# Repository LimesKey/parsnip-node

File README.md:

# parsnip-node

A rugged, self-contained Meshtastic/MeshCore LoRa node for outdoor use. It combines an
ESP32-S3 host, an Ebyte E22P-915M30S LoRa module (SX1262 + PA, up to 30 dBm / 1 W), and a
u-blox NEO-F10N dual-band (L1 + L5) GNSS receiver, and runs off two 21700 Li-ion cells
in series that charge over USB-C PD or solar. Designed in KiCad for 915 MHz operation in
Canada under ISED RSS-247.

The aim is a node that non-technical people can use without a phone: one of the
longest-range, best-value LoRa front ends, accurate GNSS, days of runtime, and protection
on every external port.

<p align="center">
  <picture>
    <source srcset="lib/img/render-spin.avif" type="image/avif">
    
  </picture>
  <br><sub>Render, see (<a href="code/render/render.sh">code/render</a>), with two 21700 cells and the optional WeAct 3.7" E-Ink module on M2 standoffs and a clear top plate. The display mount is a mock-up, not part of the board yet.</sub>
</p>

## Status

**v2 (this design):** schematic complete, PCB placed and fully routed (478 footprints, every
net one piece of copper). Prototype fab and assembly are being arranged with PCBWay.
Firmware bring-up starts once boards arrive.

**v1** (single 18650, XIAO ESP32-C6, 55 x 100 mm) was built and field-tested; photos are
at the [bottom](#v1-in-the-field). The design log is in [JOURNAL.md](JOURNAL.md).

## Features

| Block | Implementation |
| --- | --- |
| Host | ESP32-S3-WROOM-1U-N16R8 (16 MB flash, 8 MB octal PSRAM), U.FL 2.4 GHz antenna. The footprint is the WROOM-1 land pattern, so the PCB-antenna module also fits. |
| LoRa | E22P-915M30S, 915 MHz, up to 30 dBm, SMA. An antenna-detect FET inhibits TX when no antenna is attached. |
| GNSS | NEO-F10N, L1 + L5 (NEO-M9N footprint-compatible fallback). Active antenna on SMA or U.FL, switched bias-tee, dual-band SAW, 6 dB pi pad. Coin-cell backup for hot starts. |
| Battery | 2S 21700 Li-ion in SMD holders on the back. MAX17320 fuel gauge, protection and cell balancing. |
| Charger | BQ25798 buck-boost NVDC charger with dual-input power mux (USB-C or solar). Regulated ~7-8.4 V system rail. |
| USB-C | TPS25751 PD controller: sink, and source (OTG) up to 20 V @ 3 A. TPD8S300 OVP/ESD on CC/SBU, liquid detection. USB 2.0 full speed to the ESP32-S3. |
| Rails | Two LM61460 low-EMI bucks (5 V, 3.3 V), synchronised 180 deg out of phase at 2 MHz. TPS25947-family eFuses on the 5 V and GNSS rails. |
| Sensors | LSM6DSV16X 6-axis IMU, QMC6309 magnetometer. |
| I/O | 16-pin GPIO expander header (TCAL9539), Qwiic and 2.54 mm I2C ports, SPI expansion, E-Ink header, 2 x WS2816B RGB LEDs plus an external LED port, debug UART. |
| Board | 60 x 130 mm, 4 layers, 1.6 mm, ENIG, black mask. |

All charger and battery-path parts are rated for 4S (caps 25 V minimum, mostly 50 V) even
though the pack is 2S.

## Architecture

<table>
  <tr>
    <td align="center" width="50%">
      
      <br><sub><b>Block diagram</b></sub>
    </td>
    <td align="center" width="50%">
      
      <br><sub><b>Power tree</b></sub>
    </td>
  </tr>
</table>

Power flows cells -> fuse -> MAX17320 protection FETs -> BQ25798 -> **VSYS** (regulated,
not raw battery) -> the 3.3 V and 5 V bucks. The 5 V rail feeds the E22P, the LED port and
the GNSS antenna bias. The GNSS module gets its own LDO and eFuse off 5 V. USB-C (through
the PD controller) and solar each have their own FET path into the charger, and the
first valid input wins.

## Schematic

The full schematic is [parsnip-schematic.pdf](parsnip-schematic.pdf) (12 pages: cover,
block diagram, power tree, then the circuit sheets). Click a page for full size.

<table>
  <tr>
    <td align="center" width="33%">
      
      <br><sub><b>ESP32-S3 MCU</b></sub>
    </td>
    <td align="center" width="33%">
      
      <br><sub><b>LoRa (E22P-915M30S)</b></sub>
    </td>
    <td align="center" width="33%">
      
      <br><sub><b>GNSS (NEO-F10N)</b></sub>
    </td>
  </tr>
  <tr>
    <td align="center" width="33%">
      
      <br><sub><b>5 V / 3.3 V bucks</b></sub>
    </td>
    <td align="center" width="33%">
      
      <br><sub><b>Charger / power path</b></sub>
    </td>
    <td align="center" width="33%">
      
      <br><sub><b>BMS (MAX17320)</b></sub>
    </td>
  </tr>
  <tr>
    <td align="center" width="33%">
      
      <br><sub><b>USB-C / PD</b></sub>
    </td>
    <td align="center" width="33%">
      
      <br><sub><b>Peripherals</b></sub>
    </td>
    <td align="center" width="33%">
      
      <br><sub><b>Connectors</b></sub>
    </td>
  </tr>
</table>

## PCB

<table>
  <tr>
    <td align="center" width="50%">
      <a href="lib/img/render-iso.png"><picture><source srcset="lib/img/render-iso.avif" type="image/avif"></picture></a>
      <br><sub><b>Front</b></sub>
    </td>
    <td align="center" width="50%">
      <a href="lib/img/render-iso-back.png"><picture><source srcset="lib/img/render-iso-back.avif" type="image/avif"></picture></a>
      <br><sub><b>Back</b></sub>
    </td>
  </tr>
  <tr>
    <td align="center" width="50%">
      <a href="lib/img/render-top.png"><picture><source srcset="lib/img/render-top.avif" type="image/avif"></picture></a>
      <br><sub><b>Top</b></sub>
    </td>
    <td align="center" width="50%">
      <a href="lib/img/render-bottom.png"><picture><source srcset="lib/img/render-bottom.avif" type="image/avif"></picture></a>
      <br><sub><b>Bottom (21700 holders)</b></sub>
    </td>
  </tr>
</table>

- 60 x 130 mm, 4 layers, 1.6 mm total, 1 oz copper on all layers, ENIG
- Stackup (JLCPCB `JLC041611-7628` equivalent): F.Cu / 0.203 mm prepreg (Er 4.4) / In1 /
  1.03 mm core / In2 / 0.203 mm prepreg / B.Cu
- In1 is a solid GND reference for all RF. RF lines are 0.306 mm on F.Cu, 49-53 ohm
  field-solved with mask, mostly CPWG with GND via fences well under lambda/20
- ~2100 vias (0.3 mm and 0.2 mm drill), most of them GND stitching
- The cell holders take most of the back, so everything above them is single-sided

## Hardware

| Part | Price |
| --- | --- |
| PCB + assembly ([BOM](production/parsnip-bom.csv)) | being quoted |
| 2 x Samsung 58E 21700 cells [18650batterystore.com](https://www.18650batterystore.com/products/samsung-58e-21700-battery) | $40 CAD |
| WeAct 3.7" E-Ink module, 240 x 416, optional [AliExpress](https://www.aliexpress.com/item/1005009712001279.html?mp=1) | $25 CAD |

Production files (gerbers, BOM, pick-and-place) are in [production/](production/).
Datasheets for every IC, module and connector are in
[docs/datasheets/](docs/datasheets/), sources in
[SOURCES.md](docs/datasheets/SOURCES.md).

## ESP32-S3 GPIO map

GPIO numbers are ESP32-S3 GPIO, not module pins. Reference designators can change during
layout; the schematic is authoritative.

#### LoRa: E22P-915M30S

| Signal | GPIO |
| --- | --- |
| NSS | 10 |
| SCK | 12 |
| MOSI | 11 |
| MISO | 13 |
| BUSY | 14 |
| DIO1 | 4 |
| NRST | 40 |
| EN | 41 |

T/R switching comes from the module's DIO2 (`setDio2AsRfSwitch(true)`), not a GPIO.

#### GNSS: NEO-F10N

| Signal | GPIO |
| --- | --- |
| TXD (to host RX, UART1) | 1 |
| RXD (from host TX, UART1) | 2 |
| TIMEPULSE | 3 |
| EXTINT | 48 |

The module's I2C/SPI pins reach the host I2C bus only through solder jumpers, for the
NEO-M9N fallback. The F10N uses UART only.

#### Other

| Function | GPIO |
| --- | --- |
| I2C SDA / SCL (host bus) | 8 / 9 |
| I2C IRQ (PD controller, fuel gauge, GPIO expander) | 7 |
| E-Ink header: BUSY / RESET / D/C / CS | 5 / 6 / 18 / 17 |
| SPI expansion header CS | 38 |
| USB D- / D+ | 19 / 20 |
| UART0 TX / RX (debug header) | 43 / 44 |
| 32.768 kHz RTC crystal | 15 / 16 |
| BOOT | 0 |
| eFuse power-good: 5 V / GNSS 3.3 V | 39 / 42 |
| EMI sync clock gate | 47 |
| RGB LED data (via 5 V level shifter) | 46 |
| 5 V buck disable (high = off) | 21 |
| Octal PSRAM (reserved) | 35 / 36 / 37 |
| VDD_SPI strap (not connected) | 45 |

#### I2C addresses

| Bus | Device | Address |
| --- | --- | --- |
| Host (GPIO 8/9) | TPS25751 USB-PD controller | 0x20 |
| Host | MAX17320 fuel gauge | 0x36, 0x0B |
| Host | LSM6DSV16X IMU | 0x6A |
| Host | TCAL9539 GPIO expander | 0x74 |
| Host | QMC6309 magnetometer | 0x7C |
| PMIC (owned by the TPS25751) | BQ25798 charger | 0x6B |
| PMIC | M24512 EEPROM (PD config) | 0x50 |

## Firmware

Firmware is a Meshtastic fork, tracked as the `firmware` submodule
([LimesKey/firmware](https://github.com/LimesKey/firmware)). A device variant declares
the pin map above and the PA control lines so TX keys up. The GNSS is on UART1, which
stock Meshtastic supports.

```bash
git clone --recurse-submodules https://github.com/LimesKey/parsnip-node.git
```

## Repository layout

| Path | Contents |
| --- | --- |
| `parsnip.kicad_pro` | KiCad project (KiCad 10.99 nightly format; stable 10.0 cannot open it) |
| `*.kicad_sch` | Schematic sheets: seven top-level sheets plus five sub-sheets under the MCU page |
| `parsnip.kicad_pcb` | Board |
| `lib/` | Project symbols, footprints and 3D models |
| `production/` | Gerbers, BOM, pick-and-place |
| `docs/` | Datasheets and photos |
| `JOURNAL.md` | Design log |
| `v1/` | The previous single-cell board |

## v1 in the field

<table>
  <tr>
    <td align="center" width="33%">
      
      <br><sub><b>Assembled board</b></sub>
    </td>
    <td align="center" width="33%">
      
      <br><sub><b>Outdoor testing</b></sub>
    </td>
    <td align="center" width="33%">
      
      <br><sub><b>Outdoor testing, back</b></sub>
    </td>
  </tr>
</table>

## License

[CC BY-NC-SA 4.0](LICENSE)

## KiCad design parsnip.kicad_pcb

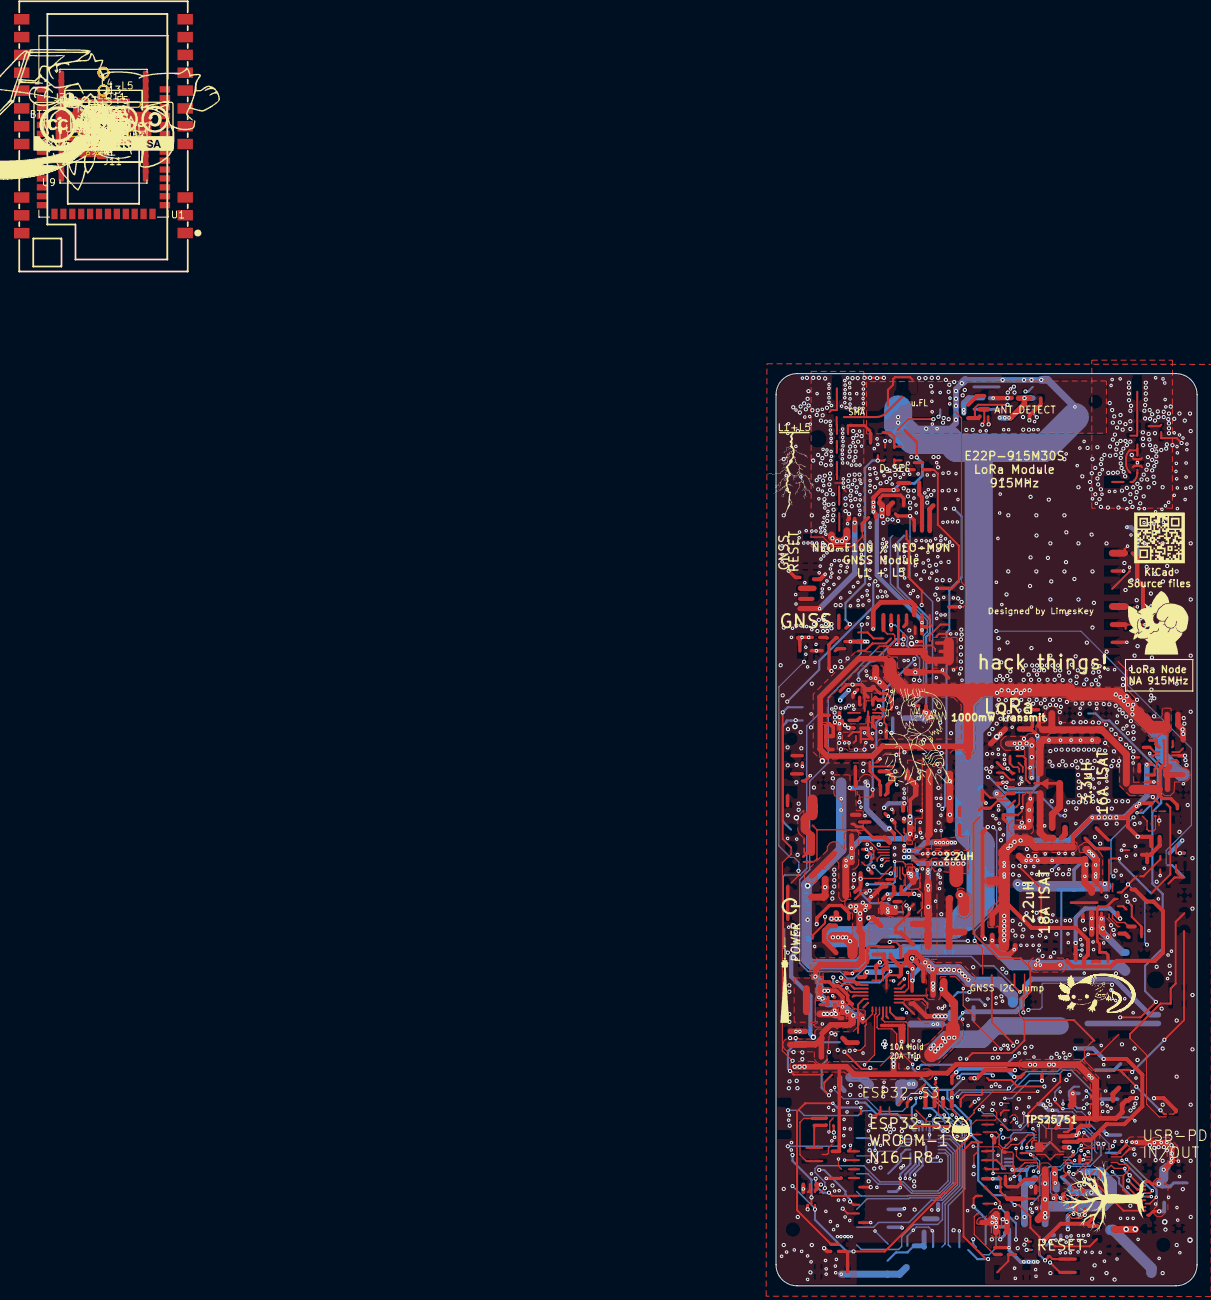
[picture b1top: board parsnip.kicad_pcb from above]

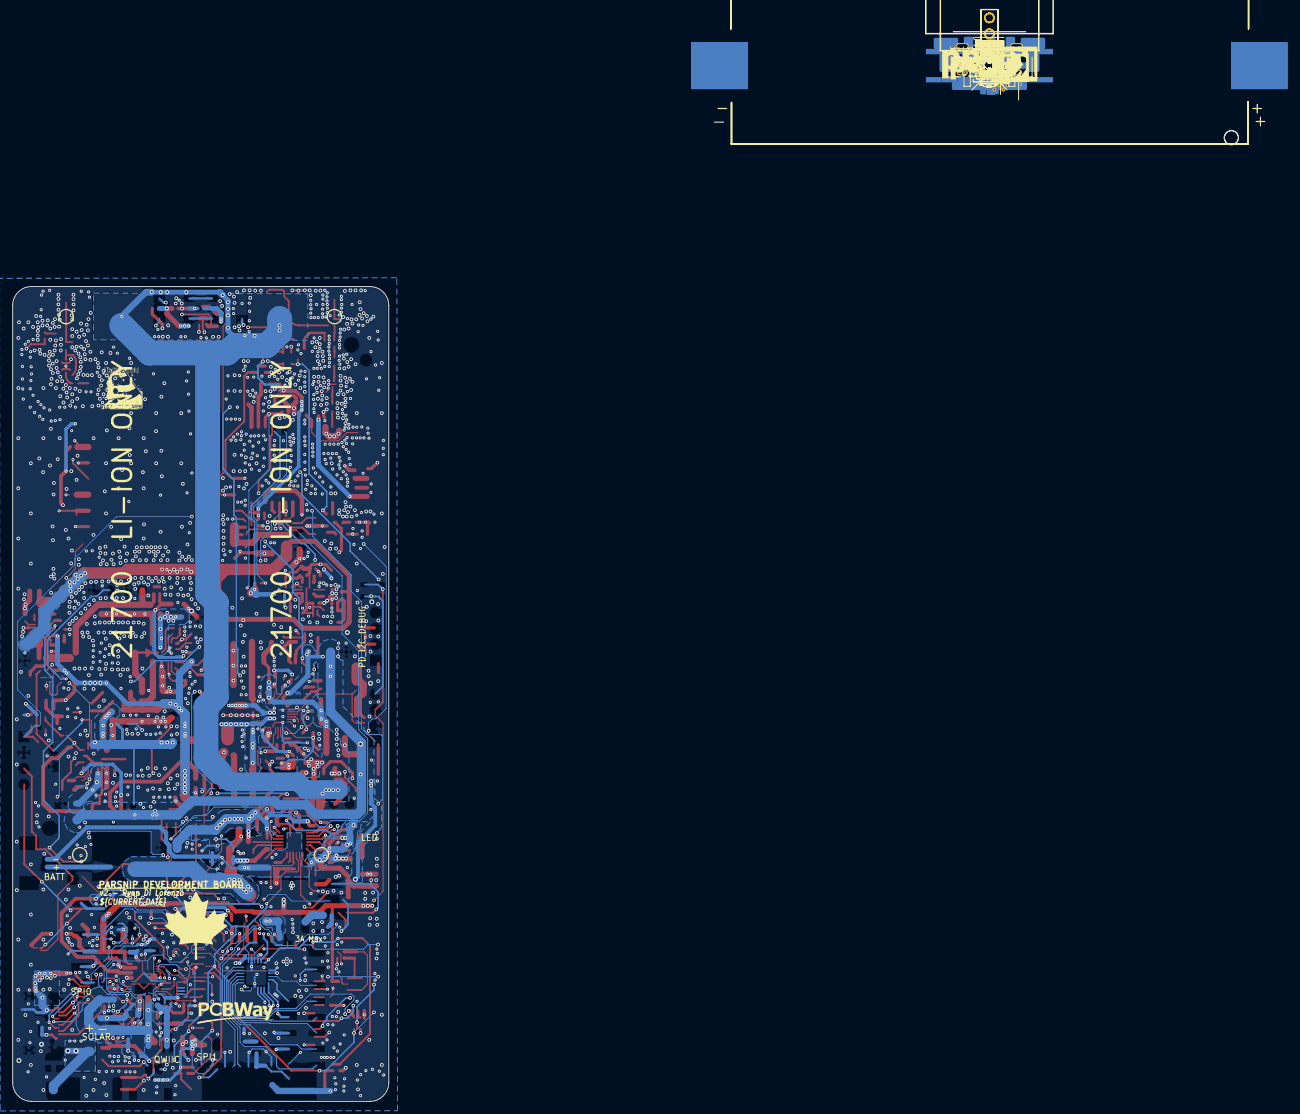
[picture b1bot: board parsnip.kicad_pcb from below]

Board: 4 copper layers, 60.0 x 130.0 mm, 472 parts (71 on the bottom side), 266 nets.

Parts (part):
BOYKISSER: LOGO
BT1, BT2: 21700 Li-ion; BAT-SMD_L82.5.5-W25-BH-21700-B1BJ001
BT3: MS621FE 5.5mAh; BatteryHolder_Seiko_MS621F
C1, C2, C3, C4, C8, C9, C13, C104, C181, C183, C193: 2.2uF; C_0402_1005Metric
C5, C19, C24, C49, C50, C51, C54, C61, C64, C66, C72, C80, C89, C116, C121, C131, C136, C184: 100nF; C_0402_1005Metric
C6, C7: 7pF; C_0402_1005Metric
C10, C11, C12, C16, C110, C122, C123, C124, C126, C127, C128, C137, C141, C143, C156, C168, C169, C177, C187, C188, C189, C190, C191, C192: 10uF; C_0603_1608Metric
C14, C38, C40, C42, C44, C67, C68, C69, C70: 10uF; C_0805_2012Metric
C17, C18, C20, C25, C39, C41, C43, C45, C46, C52, C94, C117, C118, C138, C140, C142, C163, C164, C176, C178, C179, C180, C182: 1uF; C_0402_1005Metric
C21, C22, C23, C47, C98, C105, C132, C134: 10nF; C_0402_1005Metric
C26, C27, C28, C29, C30, C32, C34, C35, C57, C59, C60, C63, C65, C71, C73, C74, C82, C84, C85, C86, C87, C88, C90, C92: 10uF; C_1206_3216Metric
C31: 4.7uF; C_0805_2012Metric
C33, C36: 330pF; C_0402_1005Metric
C37: 1uF; C_0603_1608Metric
C53, C55, C56, C58: 0.47uF; C_0402_1005Metric
C62, C79: 2.2uF; C_0805_2012Metric
C75, C76, C77: 47nF; C_0402_1005Metric
C78: 4.7uF; C_0603_1608Metric
C81: 1nF; C_0402_1005Metric_Pad0.74x0.62mm_HandSolder
C83: 470pF; C_0402_1005Metric_Pad0.74x0.62mm_HandSolder
C93: 22pF; C_0402_1005Metric
C95, C115: 47pF; C_0402_1005Metric
C96, C97: 10nF; C_0402_1005Metric_Pad0.74x0.62mm_HandSolder
C99, C100, C102, C103, C106, C107, C111, C130: 10uF; C_0402_1005Metric
C101: 4.7uF; C_0402_1005Metric
C108, C109, C161, C162: 2.2nF; C_0402_1005Metric
C112, C159, C160: 1nF; C_0402_1005Metric
C113, C114: 1pF; C_0402_1005Metric_Pad0.74x0.62mm_HandSolder
C119, C120: 22uF; C_1206_3216Metric
C125, C129, C135, C145: 2.2uF; C_0603_1608Metric
C133, C139: 220pF; C_0402_1005Metric_Pad0.74x0.62mm_HandSolder
C144, C147, C185: 22uF; C_0805_2012Metric
C153, C158: 5.6pF; C_0402_1005Metric_Pad0.74x0.62mm_HandSolder
C155, C157, C165, C166, C167, C170, C171, C186: 22uF; C_0603_1608Metric
D1, D2, D3, D26, D28, D29: ESDS314DBVR; SOT-23-5
D4, D27: 1N5819WS; D_SOD-323
D6: BZX585-C15; D_SOD-523
D7: TVS2200DRV; WSON-6-1EP_2x2mm_P0.65mm_EP1x1.6mm
D8: CHARGING; LED_0805_2012Metric
D9: SS36B; D_SMB
D10, D13: ESD501; Texas_DPY0002A_0.6x1mm_P0.65mm
D11: POWER; LED_0805_2012Metric
D12: TIMEPULSE; LED_0805_2012Metric
D14: ESD351DPYR; Texas_DPY0002A_0.6x1mm_P0.65mm
D15, D16: RB531SM-30; D_SOD-523
D17, D19: TPD1E10B06; Texas_DPY0002A_0.6x1mm_P0.65mm
D18: PGB1010603; D_0603_1608Metric_Pad1.05x0.95mm_HandSolder
D20: SMF6.0A; D_SOD-123F
D21: BAT54A; SOT-23
D22: BAT54W; SOT-323_SC-70
D23: BAT54S; SOT-23
D24, D25: PZU12B2L; D_SOD-882
F1, F7: 1A hold; Fuse_0805_2012Metric
F2: 2A hold; Fuse_0805_2012Metric
F4: 350mA hold; Fuse_0805_2012Metric
F5: 10A Hold; Fuse_2920_7451Metric
F6: 3A hold; Fuse_1812_4532Metric
FB1: BLM18HG601SN1D; L_0603_1608Metric
FID1, FID2, FID3, FID4, FID5, FID6: Fiducial; Fiducial_1mm_Mask2mm
FL1: B39162B8389P810; Filter_1411-5_1.4x1.1mm_B8389
FL2: 0900LP15B0063001E; FILTER-SMD_0805-8P-L2.0-W1.2-TL
H1, H2, H3, H4: MountingHole_Pad; MountingHole_2.2mm_M2_DIN965_Pad
J1: SPI0; HDR-SMD_6P-P2.54-H-F-W11.7
J2: I2C4; JST_SH_SM04B-SRSS-TB_1x04-1MP_P1.00mm_Horizontal
J3: I2C1; CONN-SMD_4P-P2.54_HX-PM2.54-1X4PWT
J4: I2C2; PinSocket_1x04_P2.54mm_Vertical
J5: SPI1; Molex_PicoBlade_53261-0871_1x08-1MP_P1.25mm_Horizontal
J6: UART0; JST_SH_SM03B-SRSS-TB_1x03-1MP_P1.00mm_Horizontal
J7: USB4105-GF-A-060; USB_C_Receptacle_GCT_USB4105-xx-A_16P_TopMnt_Horizontal
J8: PD_I2C DEBUG; PinSocket_1x04_P2.54mm_Vertical
J9: BAT_PORT; Molex_PicoBlade_53261-0271_1x02-1MP_P1.25mm_Horizontal
J10: SOLAR; JST_PH_S2B-PH-SM4-TB_1x02-1MP_P2.00mm_Horizontal
J11, J13: SMA-KE-347-H13.5-1.6; SMA_Samtec_SMA-J-P-H-ST-EM1_EdgeMount
J12: U.FL; U.FL_Hirose_U.FL-R-SMT-1_Vertical
J14: GPIO_Expander; HDR-SMD_16P-P2.54_HXPM2.54-2X8PWT
J15: LED 5V; JST_XH_S4B-XH-SM4-TB_1x04-1MP_P2.50mm_Horizontal
J16: I2C3; PinSocket_1x04_P2.54mm_Vertical
JP1, JP2: SolderJumper_2_Open; SolderJumper-2_P1.3mm_Open_TrianglePad1.0x1.5mm
JP3: I2C_IRQ_PULLUP; SolderJumper-2_P1.3mm_Bridged_RoundedPad1.0x1.5mm
JP4: I2C_SDA_PULLUP; SolderJumper-2_P1.3mm_Bridged_RoundedPad1.0x1.5mm
JP5: I2C_SCL_PULLUP; SolderJumper-2_P1.3mm_Bridged_RoundedPad1.0x1.5mm
JP6: WRITE_PROTECT; SolderJumper-3_P1.3mm_Bridged12_RoundedPad1.0x1.5mm_NumberL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
JP7: ZVC; SolderJumper-2_P1.3mm_Open_RoundedPad1.0x1.5mm
JP10: SolderJumper_3_Open; SolderJumper-3_P1.3mm_Open_RoundedPad1.0x1.5mm_NumberLabels
JP11: I2C/UART/SPI; SolderJumper-3_P1.3mm_Bridged12_RoundedPad1.0x1.5mm
JP12, JP16: SolderJumper_3_Bridged12; SolderJumper-3_P1.3mm_Bridged12_RoundedPad1.0x1.5mm_NumberL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
JP13: DISABLE_GNSS_PROT; SolderJumper-2_P1.3mm_Open_RoundedPad1.0x1.5mm
JP14: BYPASS_FILTER; R_0402_1005Metric
JP15: ANT_DETECT; SolderJumper-2_P1.3mm_Bridged_RoundedPad1.0x1.5mm
JP17: DISABLE_5V_PROT; SolderJumper-2_P1.3mm_Open_RoundedPad1.0x1.5mm
L1: 2.2uH; L_Sunlord_MWSA0603S
L2: 47nH; L_0603_1608Metric
L3: 470nH; L_0603_1608Metric
L4: 2.2uH; L_APV_APH1040
L5: 3.3uH; L_APV_APH1040
L6, L7: 5.1nH; L_0402_1005Metric
NT1, NT2: NetTie_3; NetTie-3_SMD_Pad0.5mm
Q1, Q3: CSD23280F3; Texas_PicoStar_DFN-3_0.69x0.60mm
Q2, Q4: CSD15380F3; Texas_PicoStar_DFN-3_0.69x0.60mm
Q5, Q6: AON7544; PQFN-8_L3.1-W3.1-P0.65-LS3.3-BL
Q7, Q8: CSD18512Q5B; VSONP-8-1EP_5x6_P1.27mm_CSD18512Q5B
Q9, Q10: SI2308; SOT-23
Q11: CSD17577Q3A; VSON-8_3.3x3.3mm_P0.65mm_NexFET
Q14, Q15: 2N7002; SOT-23
Q16: TPN2R203NC; TSON-8_L3.1-W3.1-P0.65-LS3.3-BL-EP
R1, R2, R3, R4, R23, R60: 33; R_0402_1005Metric_Pad0.72x0.64mm_HandSolder
R5, R6, R12, R13, R14, R15, R18, R19, R32, R33, R34, R69, R73, R93, R134: 0; R_0402_1005Metric
R7, R9, R35, R38, R46, R67, R71, R76, R92, R94, R101, R113, R119, R132, R135: 10k; R_0402_1005Metric
R8: 10M; R_0805_2012Metric
R10, R11: 22; R_0402_1005Metric_Pad0.72x0.64mm_HandSolder
R16, R17, R98: 22; R_0402_1005Metric
R20, R24, R25, R26, R133: 10k; R_0402_1005Metric_Pad0.72x0.64mm_HandSolder
R21, R22, R68, R72: 2.2k; R_0402_1005Metric_Pad0.72x0.64mm_HandSolder
R27, R28, R30, R56, R79, R86, R91, R96, R105, R106, R108, R130, R131, R136: 100k; R_0402_1005Metric
R29, R31, R102: 1M; R_0402_1005Metric
R36, R37: 2.2k; R_0402_1005Metric
R39, R40: 150; R_1206_3216Metric
R41: 5m; R_Shunt_0805_2012Metric_Kelvin
R42, R120: 10; R_0402_1005Metric
R43, R45, R50, R53, R78, R99: 1k; R_0402_1005Metric
R44, R48, R59, R63, R103: 100; R_0402_1005Metric
R47: 330; R_1210_3225Metric
R49, R62: 2; R_0402_1005Metric
R51: 5.23k; R_0603_1608Metric_Pad0.98x0.95mm_HandSolder
R52: 32.4k; R_0603_1608Metric_Pad0.98x0.95mm_HandSolder
R54: 24.3k; R_0603_1608Metric_Pad0.98x0.95mm_HandSolder
R55: 68.1k; R_0603_1608Metric_Pad0.98x0.95mm_HandSolder
R57, R61: 294; R_0402_1005Metric
R58: 8.2k; R_0402_1005Metric_Pad0.72x0.64mm_HandSolder
R64, R65: 2.2; R_0402_1005Metric_Pad0.72x0.64mm_HandSolder
R66: 3k; R_0402_1005Metric_Pad0.72x0.64mm_HandSolder
R70: 2k; R_0402_1005Metric
R74: 10; R_0603_1608Metric_Pad0.98x0.95mm_HandSolder
R75, R95: 0; R_0402_1005Metric_Pad0.72x0.64mm_HandSolder
R80, R83: 150; R_0402_1005Metric_Pad0.72x0.64mm_HandSolder
R81: 37.4; R_0402_1005Metric_Pad0.72x0.64mm_HandSolder
R82: 4.7k; R_0402_1005Metric
R84: 150k; R_0402_1005Metric
R85: 215k; R_0603_1608Metric_Pad0.98x0.95mm_HandSolder
R87: 113k; R_0402_1005Metric_Pad0.72x0.64mm_HandSolder
R88: 6.65k; R_0402_1005Metric_Pad0.72x0.64mm_HandSolder
R89: 200k; R_0603_1608Metric_Pad0.98x0.95mm_HandSolder
R90: 301k; R_0402_1005Metric
R100: 0; R_0805_2012Metric
R104, R107, R115, R121: 402k; R_0603_1608Metric
R109, R110: 6.04k; R_0402_1005Metric_Pad0.72x0.64mm_HandSolder
R111, R117: 100; R_0402_1005Metric_Pad0.72x0.64mm_HandSolder
R112, R118: 2.2; R_0805_2012Metric
R114: 10; R_0402_1005Metric_Pad0.72x0.64mm_HandSolder
R116: 174k; R_0402_1005Metric_Pad0.72x0.64mm_HandSolder
R122: 101k; R_0805_2012Metric_Pad1.20x1.40mm_HandSolder
R123, R124: 1k; R_0402_1005Metric_Pad0.72x0.64mm_HandSolder
R125: 86.6k; R_0402_1005Metric
R126: 3.92k; R_0402_1005Metric
R127: 27.4k; R_0402_1005Metric
R128: 549; R_0402_1005Metric_Pad0.72x0.64mm_HandSolder
R129: 280k; R_0603_1608Metric
RN1: 10k; R_Array_Concave_4x0402
SW1: ESP_RESET; SW_Push_SPST_NO_Alps_SKRK
SW2: BOOT; SW_Push_SPST_NO_Alps_SKRK
SW3: RESET; SW_Push_SPST_NO_Alps_SKRK
SW4: RESET_GNSS; SW_Push_SPST_NO_Alps_SKRK
SW5: SAFEBOOT_GNSS; SW_Push_SPST_NO_Alps_SKRK
TH1, TH2, TH3, TH4, TH5: 10k; R_0603_1608Metric
TP1: R_SENSE_SHUNT; TestPoint_2Pads_Pitch2.54mm_Drill0.8mm
TP2: IN_CP; TestPoint_2Pads_Pitch2.54mm_Drill0.8mm
TP3: REG3; TestPoint_Pad_D1.0mm
TP4: PPHV; TestPoint_2Pads_Pitch2.54mm_Drill0.8mm
TP5: CS_GPS; TestPoint_2Pads_Pitch2.54mm_Drill0.8mm
TP6: SYNC_1; TestPoint_2Pads_Pitch2.54mm_Drill0.8mm
TP7: EN_3V3; TestPoint_Pad_D1.0mm
TP8, TP9: VSYS; TestPoint_2Pads_Pitch2.54mm_Drill0.8mm
TP10, TP11: PGOOD; TestPoint_Pad_D1.5mm
TP12: 3V3; TestPoint_2Pads_Pitch2.54mm_Drill0.8mm
TP13: 5V_RAW; TestPoint_2Pads_Pitch2.54mm_Drill0.8mm
TP14: 5V; TestPoint_2Pads_Pitch2.54mm_Drill0.8mm
TP15: GPIO_EXP_RESET; TestPoint_Pad_D1.5mm
TP16: SYNC_2; TestPoint_2Pads_Pitch2.54mm_Drill0.8mm
U1: ESP32-S3-WROOM-1U-N16R8; ESP32-S3-WROOM-1
U2: QMC6309; QMC6309_WLCSP-4_0.79x0.79mm_P0.4mm
U3: TVS2200DRV; WSON-6-1EP_2x2mm_P0.65mm_EP1x1.6mm
U4: TPD8S300A; WQFN-20_L3.0-W3.0-P0.40-TL-EP1.7
U5: TPS25751DREFR; Texas_REF0038A_WQFN-38-2EP_6x4mm_P0.4
U6, U23: TPS22945DCKR; SOT-353_SC-70-5
U7: MAX17320G22+; QFN-24_L4.0-W4.0-P0.50-BL-EP2.6
U8: BQ25798; Texas_RQM0029A_VQFN-29_4x4mm_P0.4mm
U9: NEO-F10N; ublox_NEO
U10: TPS7A2033PDBVR; SOT-23-5_L2.9-W1.6-P0.95-LS2.8-BR
U11: TPS259474LRPWR; VQFN-10_L2.0-W2.0-P0.45-TL
U12: E22P-915M30S; COMM-SMD_22P-P2.54-L38.5-W24.0_E22-400M33S
U13, U14: LM61460AASQRJRRQ1; VQFN-14-HR_L4.0-W3.5-TL_LM61460AASQRJRRQ1
U15: TPS259474ARPWR; VQFN-10_L2.0-W2.0-P0.45-TL
U16: SN74LVC1G74; X2SON-8_1.4x1mm_P0.35mm
U17: TCAL9539RTWRQ1; TQFN-24_L4.0-W4.0-P0.50-BL-EP2.3
U18, U20: WS2816B; LED-SMD_6P-L5.0-W5.0-TL
U19: 74LV1T34GW; SOT-353_SC-70-5
U21: M24512-DFMC6TG; DFN-8-1EP_3x2mm_P0.5mm_EP1.36x1.46mm
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
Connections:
3V3_GNSS: C99.1, C100.1, C110.2, C111.1, D14.1 (A1), JP10.2 (C), JP13.2 (B), R67.1, R70.1, R76.1, R90.2, R91.1, R136.2, U9.23 (VCC), U11.6 (OUT)
+3V3: C1.1, C2.1, C3.1, C10.1, C11.1, C17.1, C38.1, C39.1, C121.2, C140.1, C144.1, C147.1, C163.1, C164.1, C176.1, C181.2, C183.1, C185.1, C190.2, C191.2, C192.2, C193.1, D4.2 (A), D15.2 (A), D27.2 (A), F1.2, F2.2, F7.2, JP3.2 (B), JP4.2 (B), JP5.2 (B), JP13.1 (A), L4.2, R7.1, R9.1, R24.2, R25.2, R93.1, R96.1, R102.1, R113.1, R114.2, R115.2, R119.1, R123.1, R131.2, R132.1, R133.2, TP12.2, U1.2 (3V3), U2.B1 (VDD), U5.38 (VIN_3V3), U16.6 (~CLR), U16.7 (~PRE), U16.8 (VCC), U17.21 (VCC), U22.5 (VDDIO), U22.8 (VDD), U22.12 (CS), Y2.4 (VDD)
+3V3_EXT: C8.1, C9.1, C142.1, J4.1, J16.1, U23.1 (VOUT)
+5V: C12.1, C16.1, C40.1, C41.1, C165.1, C166.1, C168.1, C169.1, C170.2, C171.2, C178.1, C179.2, C180.1, D20.1 (A1), F6.1, JP12.1 (A), JP17.2 (B), R100.1, R129.2, R134.2, TP14.2, U5.34 (PP5V), U15.6 (OUT), U18.2 (VCC), U19.5 (VCC), U20.2 (VCC)
+BATT: C54.1, C61.1, F5.2, Q5.1 (S), Q5.2 (S), Q5.3 (S)
+PACK: C61.2, C66.1, C67.1, C68.1, C69.1, C70.1, Q6.1 (S), Q6.2 (S), Q6.3 (S), Q11.5 (D), R45.2, R47.2, R63.2
-BATT: C47.2, C50.2, C51.2, C52.2, C55.1, C56.1, C58.1, C98.2, C105.2, C132.2, D6.2 (A), D23.1 (A), Q16.1 (S), Q16.2 (S), Q16.3 (S), R41.1, R43.2, R46.1, TH1.2, TH2.2, TH3.2, TH4.2, TP1.1, U7.20 (GND), U7.25 (EP)
/BMS/BMS_IN: C52.1, C53.1, D23.2 (K), R42.2, TP2.1, U7.1 (IN)
/BMS/CELL_BOT: BT2.2 (-), J9.1, Q16.5 (D), Q16.6 (D), Q16.7 (D), Q16.8 (D), Q16.9 (D)
/BMS/CELL_TOP: BT1.1 (+), F5.1, J9.2, R40.1, R42.1, R135.2
/Charger/ACDRV1: R57.2, U8.11 (ACDRV1)
/Charger/ACDRV2: R61.2, U8.10 (ACDRV2)
/Charger/CHG_BAT: C84.2, C85.2, Q11.1 (S), Q11.2 (S), Q11.3 (S), U8.22 (BAT), U8.23 (BAT)
/Charger/PMID: C80.1, C82.2, C86.2, C87.2, C88.2, U8.29 (PMID)
/Charger/REGN: C78.2, R51.2, R54.1, U8.5 (REGN)
/Charger/SW1: C75.2, L1.1, R65.1, U8.28 (SW1)
/Charger/SW2: C76.1, L1.2, R64.1, U8.26 (SW2)
/Charger/VAC1_MID: D24.2 (A), Q7.1 (S), Q8.1 (S)
/Charger/VAC2_MID: D25.2 (A), Q9.2 (S), Q10.2 (S)
/Root/BOOT: R6.2, R7.2, U1.27 (IO0)
/Root/Connectors/CS_BUS_RAW: D1.5 (I/O4), J1.6, R4.2
/Root/Connectors/I2C_HOST_SCL_RAW: D26.1 (I/O1), D26.5 (I/O4), J2.4, R60.2
/Root/Connectors/I2C_HOST_SDA_RAW: D26.3 (I/O2), D26.4 (I/O3), J2.3, R23.2
/Root/Connectors/MISO_RAW: D1.4 (I/O3), J1.5, R3.2
/Root/Connectors/MOSI_RAW: D1.3 (I/O2), J1.4, R2.2
/Root/Connectors/SCK_RAW: D1.1 (I/O1), J1.3, R1.2
/Root/Connectors/UART0_RX_RAW: D3.3 (I/O2), D3.4 (I/O3), J6.3, R17.2
/Root/Connectors/UART0_TX_RAW: D3.1 (I/O1), D3.5 (I/O4), J6.2, R16.2
/Root/EN: R5.2, R9.2, U1.3 (EN)
/Root/GNSS/D_SEL: JP11.2 (C), U9.2 (D_SEL/(F10:NC))
/Root/GNSS/EXTINT: R53.2, U9.4 (EXTINT)
/Root/GNSS/GNSS_BIAS: C95.2, L2.1, R69.2, R73.2
/Root/GNSS/GNSS_SMA: D10.2 (A2), J11.1 (In), R69.1
/Root/GNSS/GNSS_UFL: D13.1 (A1), J12.1 (In), R73.1
/Root/GNSS/LNA_EN: R78.1, U9.14 (LNA_EN)
/Root/GNSS/RXD/SPI_MOSI: R50.2, U9.21 (RXD/SPI_MOSI)
/Root/GNSS/SCL/SPI_CLK: JP2.2 (B), R72.2, U9.19 (SCL/SPI_CLK/(F10:NC))
/Root/GNSS/SDA/SPI_CS: JP1.2 (B), R68.2, TP5.2, U9.18 (SDA/~SPI_CS/(F10:NC))
/Root/GNSS/VCC_RF: C107.2, D16.2 (A), U9.9 (VCC_RF)
/Root/GPIO_3: R71.1, U1.15 (IO3), U9.3 (TIMEPULSE)
/Root/GPIO_4: U1.4 (IO4), U12.13 (DIO1)
/Root/GPIO_5: J5.1, U1.5 (IO5)
/Root/GPIO_6: J5.2, R26.1, U1.6 (IO6)
/Root/GPIO_10: R96.2, U1.18 (IO10), U12.19 (NSS)
/Root/GPIO_14: U1.22 (IO14), U12.14 (BUSY)
/Root/GPIO_17: J5.4, R24.1, U1.10 (IO17)
/Root/GPIO_18: J5.3, U1.11 (IO18)
/Root/GPIO_21: R103.1, U1.23 (IO21)
/Root/GPIO_38: R4.1, R25.1, U1.31 (IO38)
/Root/GPIO_39: R131.1, U1.32 (IO39), U15.3 (PG/AUXOFF)
/Root/GPIO_40: R19.1, U1.33 (IO40)
/Root/GPIO_41: R18.2, U1.34 (IO41)
/Root/GPIO_42: R91.2, U1.35 (IO42), U11.3 (PG/AUXOFF)
/Root/GPIO_46: U1.16 (IO46), U19.2 (A)
/Root/GPIO_47: D21.1, U1.24 (IO47)
/Root/GPIO_48: R53.1, U1.25 (IO48)
/Root/LoRa/ANT_DETECT: C112.2, Q14.1 (G), R92.1, R102.2
/Root/LoRa/EN: R18.1, R94.2, R101.1, U12.6 (EN)
/Root/LoRa/LORA_5V: C117.1, C118.1, C119.1, C120.1, D19.2 (A2), R100.2, U12.9 (VCC), U12.10 (VCC)
/Root/LoRa/LORA_ANT: C115.1, U12.21 (ANT)
/Root/LoRa/LORA_LPF_IN: C115.2, FL2.8 (IO), JP14.2 (B)
/Root/LoRa/LORA_LPF_OUT: C114.1, FL2.4 (IO), JP14.1 (A), R95.2
/Root/LoRa/LORA_SMA: C113.1, D18.2 (A2), J13.1 (In), L3.2, R95.1
/Root/LoRa/RESET: C116.1, R19.2, U12.15 (NRST)
/Root/P07: R136.1, U6.3 (OC), U17.8 (P07)
/Root/P16: D21.2, R113.2, TP10.1 (1_1), U13.5 (PGOOD), U17.16
/Root/P17: D22.3 (K), R119.2, TP11.1 (1_1), U14.5 (PGOOD), U17.17
/Root/Peripherals/LED_BDO: J15.3, U20.1 (BO), U24.2
/Root/Peripherals/LED_DO: J15.2, U20.3 (DO), U24.1
/Root/Peripherals/P00: J14.1, U17.1 (P00)
/Root/Peripherals/P01: J14.3, U17.2 (P01)
/Root/Peripherals/P02: J14.5, U17.3 (P02)
/Root/Peripherals/P03: J14.7, U17.4 (P03)
/Root/Peripherals/P04: J14.9, U17.5 (P04)
/Root/Peripherals/P05: U17.6 (P05), U22.4 (INT1)
/Root/Peripherals/P06: J14.13, U17.7 (P06)
/Root/Peripherals/P10: J14.2, U17.10
/Root/Peripherals/P11: J14.4, U17.11
/Root/Peripherals/P12: J14.6, U17.12
/Root/Peripherals/P13: J14.8, U17.13
/Root/Peripherals/P14: J14.10, U17.14
/Root/Peripherals/P15: J14.11, U17.15
/Root/Peripherals/RESET_IOEXP: R133.1, TP15.1 (1_1), U17.24 (~RESET)
/Root/Rails/5V_RAW: C155.1, C156.2, C157.1, C167.2, C186.1, C187.2, JP17.1 (A), L5.2, R120.2, R121.2, R124.1, R125.1, TP13.2, U15.5 (IN)
/Root/Rails/SYNC_1: C159.1, Q15.3 (D), R107.2, R108.1, TP6.2, U14.7 (EN/SYNC)
/Root/Rails/SYNC_2: C160.1, JP16.1 (A), TP16.2, U13.7 (EN/SYNC)
/USB Interface/CC1: C36.1, U4.12 (CC1), U5.28 (CC1)
/USB Interface/CC2: C33.1, U4.11 (CC2), U5.29 (CC2)
/USB Interface/C_CC1: J7.A5 (CC1), U4.4 (C_CC1), U4.7 (RPD_G1)
/USB Interface/C_CC2: J7.B5 (CC2), U4.5 (C_CC2), U4.6 (RPD_G2)
/USB Interface/C_SBU1: J7.A8 (SBU1), U4.1 (C_SBU1)
/USB Interface/C_SBU2: J7.B8 (SBU2), U4.2 (C_SBU2)
/USB Interface/FAULT: R27.2, U4.9 (~FLT), U5.19 (GPIO3)
/USB Interface/GPIO2: Q1.1 (G), Q2.1 (G), Q3.1 (G), Q4.1 (G), U5.7 (GPIO2)
/USB Interface/SBU1: R28.2, R29.1, U4.15 (SBU1), U5.26 (GPIO4/USB_P/LD1)
/USB Interface/SBU2: R30.2, R31.1, U4.14 (SBU2), U5.27 (GPIO5/USB_N/LD2)
/USB Interface/WC: JP6.2 (C), U21.7 (WC)
CHG_VBUS: C35.1, C71.2, C72.2, C73.2, C74.2, Q8.3 (D), Q9.3 (D), U8.2 (VBUS), U8.3 (VBUS)
C_USB_B_N: J7.B7 (D-), NT1.3, U4.16 (D4)
C_USB_B_P: J7.B6 (D+), NT2.3, U4.17 (D3)
C_USB_T_N: J7.A7 (D-), NT1.1, U4.19 (D2)
C_USB_T_P: J7.A6 (D+), NT2.1, U4.20 (D1)
GND: BT3.2 (-), C1.2, C2.2, C3.2, C4.2, C5.1, C6.2, C7.1, C8.2, C9.2, C10.2, C11.2, C12.2, C13.2, C14.2, C16.2, C17.2, C18.1, C19.2, C20.2, C21.2, C22.2, C23.2, C24.2, C25.1, C26.2, C27.2, C28.1, C29.2, C30.2, C31.1, C32.2, C33.2, C34.2, C35.2, C36.2, C37.2, C38.2, C39.2, C40.2, C41.2, C42.2, C43.2, C44.2, C45.2, C46.1, C57.1, C59.1, C60.1, C62.2, C63.1, C64.2, C65.1, C66.2, C67.2, C68.2, C69.2, C70.2, C71.1, C72.1, C73.1, C74.1, C77.2, C78.1, C79.2, C80.2, C81.2, C82.1, C83.2, C84.1, C85.1, C86.1, C87.1, C88.1, C89.2, C90.2, C92.2, C93.2, C94.2, C96.2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
GPS_ANT: R81.2, R83.2, U9.11 (RF_IN)
I2C_HOST_IRQ: R20.1, U1.7 (IO7), U5.10 (~I2Ct_IRQ), U7.7 (ALRT), U17.22 (~INT)
I2C_HOST_SCL: D2.1 (I/O1), D28.1 (I/O1), D28.5 (I/O4), D29.1 (I/O1), D29.5 (I/O4), J3.4, J4.3, J16.3, JP2.1 (A), R22.1, R60.1, U1.17 (IO9), U2.A2 (SCL), U5.9 (I2Ct_SCL), U7.8 (SCL/DOD), U17.19 (SCL), U22.13 (SCL)
I2C_HOST_SDA: D2.3 (I/O2), D28.3 (I/O2), D28.4 (I/O3), D29.3 (I/O2), D29.4 (I/O3), J3.2, J4.4, J16.4, JP1.1 (A), R21.1, R23.1, U1.12 (IO8), U2.B2 (SDA), U5.8 (I2Ct_SDA), U7.9 (SDA/DQ), U17.20 (SDA), U22.14 (SDA)
I2C_PMIC_IRQ: R35.2, U5.18 (~I2Cc_IRQ), U8.21 (~INT)
I2C_PMIC_SCL: R32.1, R36.2, U5.17 (I2Cc_SCL), U8.14 (SCL), U21.6 (SCL)
I2C_PMIC_SDA: R33.1, R37.2, U5.16 (I2Cc_SDA), U8.15 (SDA), U21.5 (SDA)
MISO: R3.1, R98.1, U1.21 (IO13)
MOSI: J5.6, R2.1, R10.1, U12.17 (MOSI)
unnamed: BT1.2 (-), BT2.1 (+), R39.1
unnamed: C5.2, R6.1, SW2.2
unnamed: C6.1, R8.2, R12.1, Y1.1
unnamed: C7.2, R8.1, R13.1, Y1.2
unnamed: C62.1, R49.2
unnamed: C79.1, R62.2
unnamed: C81.1, R64.2
unnamed: C83.1, R65.2
unnamed: C93.1, C94.1, L2.2, R74.1
unnamed: C95.1, C96.1, R75.1
unnamed: C97.1, FL1.1, L6.1, R75.2
unnamed: C133.1, R112.2
unnamed: C139.1, R118.2
unnamed: C153.1, R123.2
unnamed: C158.1, R124.2
unnamed: C182.2, R5.1, SW1.2
unnamed: D4.1 (K), F4.2
unnamed: D6.1 (K), Q16.4 (G), R135.1
unnamed: D8.1 (K), R66.1
unnamed: D11.2 (A), R70.2
unnamed: D12.2 (A), R71.2
unnamed: D15.1 (K), R82.1
unnamed: D16.1 (K), JP12.3 (B)
unnamed: C106.2, C130.1, D17.1 (A1), R84.1, R85.1, U10.5 (OUT), U11.5 (IN)
unnamed: D21.3, D22.1 (A), R132.2, Y2.1 (~ST)
unnamed: C49.2, C50.1, D23.3 (COM), R39.2, U7.21 (CELL1)
unnamed: D24.1 (K), Q7.2 (G), Q8.2 (G), R57.1
unnamed: D25.1 (K), Q9.1 (G), Q10.1 (G), R61.1
unnamed: C4.1, D27.1 (K), U23.4 (ON), U23.5 (VIN)
unnamed: FL1.4, L7.1, R80.2, R81.1
unnamed: F1.1, J1.1
unnamed: F7.1, J2.2
unnamed: F2.1, J3.1
unnamed: C13.1, C14.1, F4.1, J5.8
unnamed: J8.1, R34.1
unnamed: J8.2, R32.2
unnamed: J8.3, R33.2
unnamed: C137.1, F6.2, J15.1
unnamed: JP3.1 (A), R20.2
unnamed: JP4.1 (A), R21.2
unnamed: JP5.1 (A), R22.2
unnamed: JP6.1 (A), RN1.8 (R1.2)
unnamed: JP6.3 (B), R38.1
unnamed: JP7.1 (A), U7.5 (ZVC)
unnamed: JP7.2 (B), R47.1
unnamed: JP10.1 (A), R72.1
unnamed: JP10.3 (B), R68.1
unnamed: JP11.1 (A), R67.2
unnamed: FB1.2, JP12.2 (C)
unnamed: JP15.2 (B), Q14.2 (S)
unnamed: JP16.3 (B), TP7.1 (1_1)
unnamed: JP16.2 (C), R104.2, R105.1
unnamed: L3.1, R92.2
unnamed: Q1.3 (D), R28.1
unnamed: Q2.3 (D), R29.2
unnamed: Q3.3 (D), R30.1
unnamed: Q4.3 (D), R31.2
unnamed: Q5.5 (D), Q5.6 (D), Q5.7 (D), Q5.8 (D), Q6.5 (D), Q6.6 (D), Q6.7 (D), Q6.8 (D)
unnamed: C54.2, Q5.4 (G), R44.2
unnamed: Q6.4 (G), R48.2
unnamed: Q11.4 (G), U8.24 (SDRV)
unnamed: Q14.3 (D), R99.2, U12.7 (T/RCTRL)
unnamed: Q15.1 (G), R103.2, R106.1
unnamed: R59.1, SW3.2
unnamed: R93.2, R94.1
unnamed: RN1.7 (R2.2), U21.1 (E0)
unnamed: RN1.6 (R3.2), U21.2 (E1)
unnamed: RN1.5 (R4.2), U21.3 (E2)
unnamed: R10.2, U1.19 (IO11)
unnamed: R11.2, U1.20 (IO12)
unnamed: R12.2, U1.8 (IO15)
unnamed: R13.2, U1.9 (IO16)
unnamed: R15.1, U1.14 (USB_D+)
unnamed: R14.1, U1.13 (USB_D-)
unnamed: C19.1, U4.3 (VBIAS)
unnamed: U5.15 (DRAIN), U5.30 (DRAIN), U5.40 (DRAIN)
unnamed: C42.1, C43.1, U5.4 (LDO_1V5)
unnamed: R78.2, R79.2, U6.4 (ON)
unnamed: C101.1, FB1.1, U6.5 (VIN)
unnamed: C138.1, R74.2, U6.1 (VOUT)
unnamed: C58.2, R46.2, U7.12 (AOLDO)
unnamed: C49.1, C51.1, R40.2, U7.22 (CELL2), U7.23 (CELL3), U7.24 (BATTS)
unnamed: R44.1, U7.3 (CHG)
unnamed: C53.2, TP2.2, U7.2 (CP)
unnamed: R41.3, U7.14 (CSN)
unnamed: R41.2, U7.15 (CSP)
unnamed: R48.1, U7.4 (DIS)
unnamed: R45.1, U7.6 (PCKP)
unnamed: R43.1, U7.11 (PFAIL)
unnamed: C55.2, U7.17 (REG2)
unnamed: C56.2, TP3.1 (1_1), U7.13 (REG3)
unnamed: C98.1, TH1.1, U7.10 (TH1)
unnamed: C132.1, TH2.1, U7.16 (TH2)
unnamed: C105.1, TH3.1, U7.18 (TH3)
unnamed: C47.1, TH4.1, U7.19 (TH4)
unnamed: C77.1, R63.1, U8.18 (BATP)
unnamed: C75.1, U8.4 (BTST1)
unnamed: C76.2, U8.19 (BTST2)
unnamed: R54.2, R55.1, U8.17 (ILIM_HIZ)
unnamed: R58.2, U8.20 (PROG)
unnamed: R66.2, U8.1 (STAT)
unnamed: C134.1, R51.1, R52.2, TH5.1, U8.16 (TS)
unnamed: R56.2, U8.13 (~CE)
unnamed: R59.2, U8.12 (~QON)
unnamed: R76.2, SW4.2, U9.8 (~RESET)
unnamed: SW5.2, U9.1 (~SAFEBOOT)
unnamed: C104.1, R134.1, U10.1 (IN), U10.3 (EN)
unnamed: C109.2, U11.7 (DVDT)
unnamed: R84.2, R86.1, U11.1 (EN/UVLO)
unnamed: R88.2, U11.9 (ILM)
unnamed: C108.1, U11.10 (ITIMER)
unnamed: R85.2, R87.1, U11.2 (OVLO/OVCSEL)
unnamed: R89.2, R90.1, U11.4 (PGTH/~FLT)
unnamed: R99.1, U12.8 (DIO2)
unnamed: R98.2, U12.16 (MISO)
unnamed: C135.2, R114.1, U13.1 (BIAS)
unnamed: C131.2, R111.1, U13.14 (CBOOT)
unnamed: C153.2, R115.1, R116.2, U13.4 (FB)
unnamed: R111.2, U13.13 (RBOOT)
unnamed: R109.2, U13.6 (RT)
unnamed: C131.1, L4.1, R112.1, U13.10 (SW)
unnamed: C125.1, U13.2 (VCC)
unnamed: C145.2, R120.1, U14.1 (BIAS)
unnamed: C136.2, R117.1, U14.14 (CBOOT)
unnamed: C158.2, R121.1, R122.2, U14.4 (FB)
unnamed: R117.2, U14.13 (RBOOT)
unnamed: R110.2, U14.6 (RT)
unnamed: C136.1, L5.1, R118.1, U14.10 (SW)
unnamed: C129.1, U14.2 (VCC)
unnamed: C162.2, U15.7 (DVDT)
unnamed: R125.2, R126.1, U15.1 (EN/UVLO)
unnamed: R128.1, U15.9 (ILM)
unnamed: C161.2, U15.10 (ITIMER)
unnamed: R126.2, R127.1, U15.2 (OVLO/OVCSEL)
unnamed: R129.1, R130.1, U15.4 (PGTH/~FLT)
unnamed: U16.1 (C), Y2.3 (OUT)
unnamed: C159.2, U16.2 (D), U16.3 (~Q)
unnamed: C160.2, U16.5 (Q)
unnamed: U18.1 (BO), U20.6 (BI)
unnamed: U18.4 (DI), U19.4 (Y)
unnamed: U18.3 (DO), U20.4 (DI)
PD_LDO_3V3: C18.2, C20.1, C25.2, C44.1, C45.1, C46.2, D8.2 (A), J8.4, Q1.2 (S), Q3.2 (S), R27.1, R35.1, R36.1, R37.1, R38.2, U4.10 (VPWR), U5.1 (LDO_3V3), U5.2 (ADCIN1), U21.8 (VCC)
PPHV: C26.1, C27.1, C28.2, C29.1, C30.1, C32.1, C34.1, C37.1, C64.1, Q7.3 (D), R49.1, TP4.2, U5.20 (PPHV), U8.9 (VAC1)
SCK: J5.5, R1.1, R11.1, U12.18 (SCK)
SOLAR: C90.1, D7.4 (IN), D7.5 (IN), D7.6 (IN), D9.1 (K), J10.1, Q10.3 (D), R62.1, U8.8 (VAC2)
UART0_RX: R17.1, U1.36 (RXD0)
UART0_TX: R16.1, U1.37 (TXD0)
UART1_RX: U1.39 (IO1), U9.20 (TXD/SPI_MISO)
UART1_TX: R50.1, U1.38 (IO2)
USB D+: NT2.2, R15.2
USB D-: NT1.2, R14.2
VBUS: C21.1, C22.1, C23.1, C24.1, C31.2, C184.1, J7.A4 (VBUS), J7.A9 (VBUS), J7.B4 (VBUS), J7.B9 (VBUS), U3.4 (IN), U3.5 (IN), U3.6 (IN), U5.23 (VBUS_IN), U5.32 (VBUS)
VSYS: C57.2, C59.2, C60.2, C63.2, C65.2, C89.1, C92.1, C122.2, C123.2, C124.2, C126.2, C127.2, C128.2, C141.1, C143.2, C177.1, C188.1, C189.1, R104.1, R107.1, TP8.1, TP9.1, U8.25 (SYS), U13.8 (VIN1), U13.12 (VIN2), U14.8 (VIN1), U14.12 (VIN2)
V_BCKP: BT3.1 (+), C102.2, C103.2, R82.2, U9.22 (V_BCKP)

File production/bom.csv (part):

"Reference","Qty","Value","Description","Manufacturer","MPN","LCSC Part","Footprint","DNP","Datasheet","Dielectric","Power Rating","Note"
"R5,R6,R12,R13,R14,R15,R18,R19,R32,R33,R34,R69,R134","13","0","RES 0Ω jumper 0402","Vishay","CRCW04020000Z0EDHP","C844711","Resistor_SMD:R_0402_1005Metric","","https://datasheet.lcsc.com/datasheet/pdf/26cdfc55b8426b7658f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","","",""
"R73,R93","2","0","RES 0Ω jumper 0402","Vishay","CRCW04020000Z0EDHP","C844711","Resistor_SMD:R_0402_1005Metric","DNP","https://datasheet.lcsc.com/datasheet/pdf/26cdfc55b8426b7658f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","","",""
"R75,R95","2","0","RES 0Ω jumper 0402","Vishay","CRCW04020000Z0EDHP","C844711","Resistor_SMD:R_0402_1005Metric_Pad0.72x0.64mm_HandSolder","","https://datasheet.lcsc.com/datasheet/pdf/26cdfc55b8426b7658f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","","",""
"R100","1","0","RES 0Ω jumper 0805","UNI-ROYAL","0805W8F0000T5E","C17477","Resistor_SMD:R_0805_2012Metric","","https://datasheet.lcsc.com/datasheet/pdf/0a975aaa49b7c97f38a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","","",""
"C113,C114","2","1pF","CAP MLCC 1pF 0402, DNP placeholder (no part assigned)","","","","Capacitor_SMD:C_0402_1005Metric_Pad0.74x0.62mm_HandSolder","DNP","","C0G","",""
"C153,C158","2","5.6pF","CAP MLCC 5.6pF 50V C0G 0402","PSA (Prosperity Dielectrics)","FN15N5R6D500PNG","C525219","Capacitor_SMD:C_0402_1005Metric_Pad0.74x0.62mm_HandSolder","","https://datasheet.lcsc.com/datasheet/pdf/3d771c0c586676719f8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","C0G","",""
"C6,C7","2","7pF","CAP MLCC 7pF 50V C0G 0402","PSA (Prosperity Dielectrics)","FN15N7R0D500PNG","C2929131","Capacitor_SMD:C_0402_1005Metric","","https://datasheet.lcsc.com/datasheet/pdf/2861834283c8f361683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","C0G","",""
"C93","1","22pF","CAP MLCC 22pF ±5% 50V C0G 0402","CCTC","TCC0402COG220J500AT","C696857","Capacitor_SMD:C_0402_1005Metric","","https://datasheet.lcsc.com/datasheet/pdf/960fc76f20dcdbc93ff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","C0G","",""
"C95,C115","2","47pF","CAP MLCC 47pF ±5% 50V C0G 0402","HRE","CGA0402C0G470J500GT","C20069324","Capacitor_SMD:C_0402_1005Metric","","https://datasheet.lcsc.com/datasheet/pdf/dc7c513e4a82d65cc37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","C0G","",""
"C133,C139","2","220pF","CAP MLCC 220pF 0402, DNP placeholder (no part assigned)","","","","Capacitor_SMD:C_0402_1005Metric_Pad0.74x0.62mm_HandSolder","DNP","","","",""
"C33,C36","2","330pF","CAP MLCC 330pF ±1% 50V C0G 0402","CCTC","TCC0402COG331F500AT","C53426851","Capacitor_SMD:C_0402_1005Metric","","https://datasheet.lcsc.com/datasheet/pdf/71a9f8eccc4da164324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","C0G","",""
"C83","1","470pF","CAP MLCC 1nF 0402, DNP placeholder (no part assigned)","","","","Capacitor_SMD:C_0402_1005Metric_Pad0.74x0.62mm_HandSolder","DNP","","","",""
"C81","1","1nF","CAP MLCC 1nF 0402, DNP placeholder (no part assigned)","","","","Capacitor_SMD:C_0402_1005Metric_Pad0.74x0.62mm_HandSolder","DNP","","","",""
"C112,C159,C160","3","1nF","CAP MLCC 1nF ±5% 50V C0G 0402","TORCH","CC0402CG50V102JN","C54916656","Capacitor_SMD:C_0402_1005Metric","","https://datasheet.lcsc.com/datasheet/pdf/49b70b003dccd16cc3f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","C0G","",""
"C108,C109,C161,C162","4","2.2nF","CAP MLCC 2.2nF ±2% 50V C0G 0402","Murata","GRM1555C1H222GA01D","C2987940","Capacitor_SMD:C_0402_1005Metric","","https://datasheet.lcsc.com/datasheet/pdf/ae687d21155af07a1c7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","C0G","",""
"L6,L7","2","5.1nH","IND RF 5.1nH, 600mA, 130mΩ, multilayer, 0402","TDK","MLG1005S5N1CTD25","C404625","Inductor_SMD:L_0402_1005Metric","","https://datasheet.lcsc.com/datasheet/pdf/fe4699cfe0567e4501e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","","","Q=42 @ 1.8GHz"
"C21,C22,C23,C47,C98,C105,C132,C134","8","10nF","CAP MLCC 10nF ±20% 50V X7R 0402","CCTC","TCC0402X7R103M500AT","C696856","Capacitor_SMD:C_0402_1005Metric","","https://datasheet.lcsc.com/datasheet/pdf/960fc76f20dcdbc93ff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","X7R","",""
"C96,C97","2","10nF","CAP MLCC 10nF ±20% 50V X7R 0402","CCTC","TCC0402X7R103M500AT","C696856","Capacitor_SMD:C_0402_1005Metric_Pad0.74x0.62mm_HandSolder","DNP","https://datasheet.lcsc.com/datasheet/pdf/960fc76f20dcdbc93ff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","X7R","",""
"C75,C76,C77","3","47nF","CAP MLCC 47nF ±10% 50V X7R 0402","CCTC","TCC0402X7R473K500AT","C880605","Capacitor_SMD:C_0402_1005Metric","","https://datasheet.lcsc.com/datasheet/pdf/960fc76f20dcdbc93ff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","X7R","",""
"L2","1","47nH","IND RF 47nH ±2%, 380mA, 290mΩ, wirewound, 0603","Murata","LQW18AN47NG00D","C98076","Inductor_SMD:L_0603_1608Metric","","https://datasheet.lcsc.com/datasheet/pdf/d18d069bcb310402631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","","","SRF >= 2GHz"
"C5,C19,C24,C49,C50,C51,C54,C61,C64,C66,C72,C80,C89,C116,C121,C131,C136,C184","18","100nF","CAP MLCC 100nF ±5% 50V X7R 0402","FH (Fenghua)","0402B104J500NT","C5272680","Capacitor_SMD:C_0402_1005Metric","","https://datasheet.lcsc.com/datasheet/pdf/09fe2daf22580a99fa7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","X7R","",""
"C53,C55,C56","3","0.47uF","CAP MLCC 470nF ±10% 25V X5R 0402","Chinocera","HGC0402R5474K250NTEJ","C49333230","Capacitor_SMD:C_0402_1005Metric","","https://datasheet.lcsc.com/datasheet/pdf/61633b63ed3f06bbdb1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","X5R","",""
"C58","1","0.47uF","CAP MLCC 470nF ±10% 25V X5R 0402","Chinocera","HGC0402R5474K250NTEJ","C49333230","Capacitor_SMD:C_0402_1005Metric","DNP","https://datasheet.lcsc.com/datasheet/pdf/61633b63ed3f06bbdb1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","X5R","",""
"L3","1","470nH","IND RF 470nH ±2%, 75mA, 7Ω, wirewound, 0603","Murata","LQW18ANR47G00D","C113132","Inductor_SMD:L_0603_1608Metric","","https://datasheet.lcsc.com/datasheet/pdf/d18d069bcb310402631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","","",""
"C17,C18,C20,C25,C39,C41,C43,C45,C46,C94,C138,C140,C142,C163,C164,C176,C178,C179,C180,C182","20","1uF","CAP MLCC 1uF ±10% 25V X7R 0402","CCTC","TCC0402X7R105K250AT","C53426846","Capacitor_SMD:C_0402_1005Metric","","https://datasheet.lcsc.com/datasheet/pdf/71a9f8eccc4da164324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","X7R","",""
"C37","1","1uF","CAP MLCC 1uF ±10% 50V X7R 0603","Chinocera","HGC0603R7105K500NTHJ","C7432774","Capacitor_SMD:C_0603_1608Metric","","https://datasheet.lcsc.com/datasheet/pdf/3025399970486160f96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","X7R","",""
"C52,C117,C118","3","1uF","CAP MLCC 1uF ±10% 50V X5R 0402","Chinocera","HGC0402R5105K500NTEJ","C7472948","Capacitor_SMD:C_0402_1005Metric","","https://datasheet.lcsc.com/datasheet/pdf/3025399970486160f96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","X5R","",""
"L4","1","2.2uH","IND POWER 2.2uH ±20%, Isat 18A, Irms 12A, 5.8mΩ, shielded, 10.8x10mm","Cybermax","CMLO1040H2R2MTT","C439019","Inductor_SMD:L_APV_APH1040","","https://datasheet.lcsc.com/datasheet/pdf/7029bbea28904fe50f5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","","",""
"C1,C2,C3,C4,C8,C9,C13,C104,C181,C183,C193","11","2.2uF","CAP MLCC 2.2uF ±10% 35V X5R 0402","Chinocera","HGC0402R5225K350NTEJ","C33546001","Capacitor_SMD:C_0402_1005Metric","","https://datasheet.lcsc.com/datasheet/pdf/f608324e16dc58a8d3b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","X5R","",""
"L1","1","2.2uH","IND POWER 2.2uH ±20%, Isat 10A, Irms 8A, 15mΩ, molded, 7.1x6.6mm","Sunlord","TMPA0603S-2R2MN-D","C357100","Inductor_SMD:L_Sunlord_MWSA0603S","","https://datasheet.lcsc.com/datasheet/pdf/5f2e591fa661f4b59d5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","","",""
"C62,C79","2","2.2uF","CAP MLCC 2.2uF ±10% 50V X7R 0805","Samwha","CS2012X7R225K500NRE","C17702473","Capacitor_SMD:C_0805_2012Metric","","https://datasheet.lcsc.com/datasheet/pdf/de3131a7974cb4c7233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","X7R","",""
"C125,C129,C135,C145","4","2.2uF","CAP MLCC 2.2uF ±10% 50V X5R 0603","Chinocera","HGC0603R5225K500NTHJ","C7432769","Capacitor_SMD:C_0603_1608Metric","","https://datasheet.lcsc.com/datasheet/pdf/3025399970486160f96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","X5R","",""
"L5","1","3.3uH","IND POWER 3.3uH ±20%, Isat 16A, Irms 10A, 10mΩ, shielded, 10.8x10mm","Cybermax","CMLO1040H3R3MTT","C439020","Inductor_SMD:L_APV_APH1040","","https://datasheet.lcsc.com/datasheet/pdf/7029bbea28904fe50f5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","","",""
"C31","1","4.7uF","CAP MLCC 4.7uF ±10% 50V X7R 0805","Chinocera","HGC0805R7475K500NSLJ","C7472970","Capacitor_SMD:C_0805_2012Metric","","https://datasheet.lcsc.com/datasheet/pdf/3025399970486160f96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","X7R","",""
"C78","1","4.7uF","CAP MLCC 4.7uF ±10% 35V X5R 0603","Chinocera","HGC0603R5475K350NTHJ","C22367829","Capacitor_SMD:C_0603_1608Metric","","https://datasheet.lcsc.com/datasheet/pdf/c406d44fbf95883b4a8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","X5R","",""
"C101","1","4.7uF","CAP MLCC 4.7uF ±20% 25V X5R 0402","HRE","CGA0402X5R475M250GT","C6119795","Capacitor_SMD:C_0402_1005Metric","","https://datasheet.lcsc.com/datasheet/pdf/b1266b0c87197fb3f02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","X5R","",""
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

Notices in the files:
parts and their libraries:
Creative Commons BY-NC-SA 4.0 badge (CC press kit 88x31 SVG), silkscreen only
